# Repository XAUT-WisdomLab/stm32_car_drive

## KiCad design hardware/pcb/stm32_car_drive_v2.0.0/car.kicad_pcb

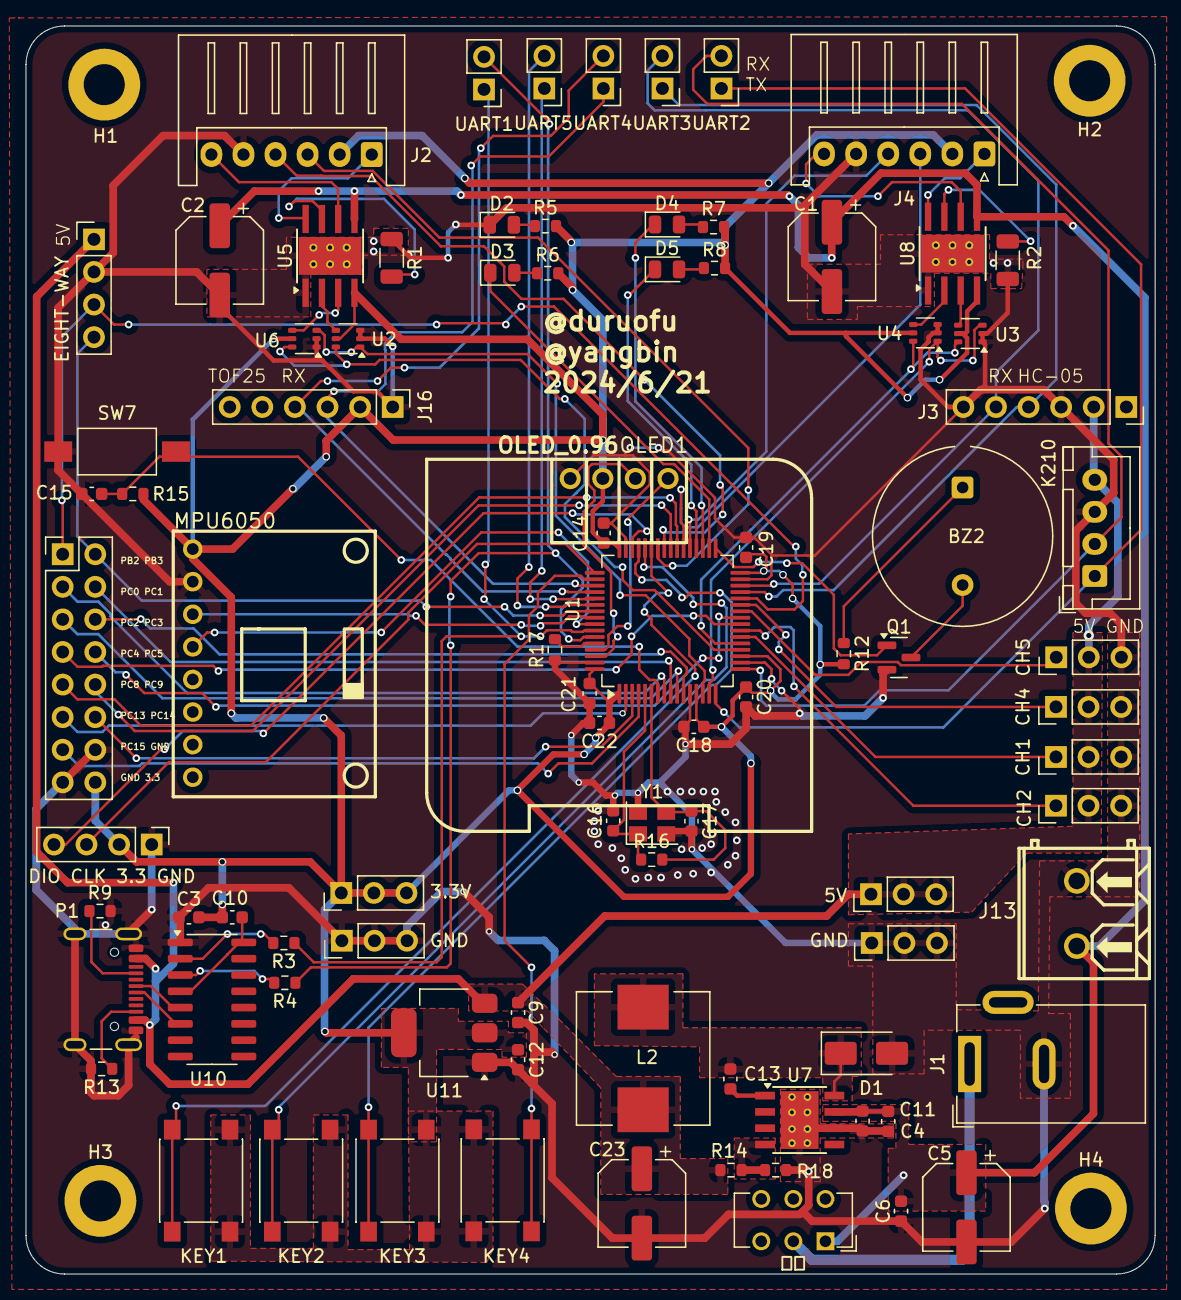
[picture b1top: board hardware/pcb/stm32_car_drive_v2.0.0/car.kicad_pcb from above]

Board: 2 copper layers, 88.0 x 97.3 mm, 92 parts (0 on the bottom side), 84 nets.

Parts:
3.3V, 5V: Conn_01x03; PinHeader_1x03_P2.54mm_Vertical
BZ2: Buzzer; Indicator_PUI_AI-1440-TWT-24V-2-R
C1, C2: 100uf; CP_Elec_6.3x7.7
C3: 0.1uF; C_0603_1608Metric
C4, C11: 4.7uf; C_0603_1608Metric
C5, C23: 220uf; CP_Elec_6.3x7.7
C6, C10: 0.1uf; C_0603_1608Metric
C9, C12: 2.2uF; C_0603_1608Metric
C13: 0.01uf; C_0603_1608Metric
C14, C18, C19, C20, C21, C22: 0.1uf/16V; C_0603_1608Metric
C15: 0.1uF/50V; C_0603_1608Metric
C16, C17: 22pf/16V; C_0603_1608Metric
CH1, CH2, CH4, CH5: Conn_01x03; PinHeader_1x03_P2.54mm_Vertical
D1: B340; D_SMA
D2, D3, D4, D5: LED; LED_0805_2012Metric
DIO CLK 3.3 GND: Conn_01x04; PinHeader_1x04_P2.54mm_Vertical
EIGHT-WAY: Conn_01x04; PinHeader_1x04_P2.54mm_Vertical
GND: Conn_01x03; PinHeader_1x03_P2.54mm_Vertical
GND#2: Conn_01x03; PinHeader_1x03_P2.54mm_Vertical
H1, H2, H3, H4: MountingHole; MountingHole_3.2mm_M3_DIN965_Pad
J1: DC母座(大)
J2, J4: Conn_01x06; JST_XH_S6B-XH-A_1x06_P2.50mm_Horizontal
J3: HC-05; PinSocket_1x06_P2.54mm_Vertical
J13: Conn_01x02; CONN-TH_2P-P5.08
J16: HC-05; PinHeader_1x06_P2.54mm_Vertical
K210: Conn_01x04; JST_XH_B4B-XH-A_1x04_P2.50mm_Vertical
KEY1: K1; SW_Push_1P1T_NO_6x6mm
KEY2: K2; SW_Push_1P1T_NO_6x6mm
KEY3: K3; SW_Push_1P1T_NO_6x6mm
KEY4: K4; SW_Push_1P1T_NO_6x6mm
L2: 22uh; L_Wuerth_HCI-1040
MPU6050: Conn_01x08; MPU6050-GY-521
OLED1: OLED_0.96; 0.96OLED_4P
P1: USB_C_Plug_USB2.0; USB_C_Receptacle_GCT_USB4105-xx-A_16P_TopMnt_Horizontal
PB2 PB3: Conn_02x08_Counter_Clockwise; PinHeader_2x08_P2.54mm_Vertical
Q1: S8050; SOT-23
R1, R2: 0.15R 1206 1WOCP=3.3V/10/0.15R=2.2A; R_1206_3216Metric
R3, R4: 0; R_0603_1608Metric
R5, R6, R7, R8, R17: 10k; R_0603_1608Metric
R9, R13: 5.1K; R_0603_1608Metric
R12: 20; R_0603_1608Metric
R14: R; R_0603_1608Metric
R15: 10K; R_0603_1608Metric
R16: 1M; R_0603_1608Metric
R18: 3.2k; R_0603_1608Metric
SW7: RST; SW_SPST_FSMSM
U1: STM32F103RCTx; LQFP-64_10x10mm_P0.5mm
U2, U3, U4, U6: SOT-363_SC-70-6
U5, U8: DRV8870DDA; Texas_HTSOP-8-1EP_3.9x4.9mm_P1.27mm_EP2.95x4.9mm_Mask2.4x3.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
U7: TPS5430DDA; TI_SO-PowerPAD-8_ThermalVias
U10: CH340C; SOIC-16_3.9x9.9mm_P1.27mm
U11: SGM2212-3.3XKC3G/TR; SOT-223
UART1, UART2, UART3, UART4, UART5: Conn_01x02; PinHeader_1x02_P2.54mm_Vertical
Y1: Crystal_GND24(8M); Crystal_SMD_3225-4Pin_3.2x2.5mm
电源: SW_Push_SPDT; SW_CuK_JS202011CQN_DPDT_Straight

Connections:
+3.3V: 3.3V.1, 3.3V.2, 3.3V.3, C3.2, C10.2, C12.1, C14.1, C18.1, C19.1, C20.1, C21.1, C22.1, DIO CLK 3.3 GND.2, J2.2, J4.2, J16.2, KEY1.2, KEY2.2, KEY3.2, KEY4.2, MPU6050.1, OLED1.2 (VCC), PB2 PB3.16, R5.2, R6.2, R7.2, R8.2, R12.2, R15.2, U1.1 (VBAT), U1.13 (VDDA), U1.19 (VDD), U1.32 (VDD), U1.48 (VDD), U1.64 (VDD), U2.5, U3.5, U4.5, U5.4 (VREF), U6.5, U8.4 (VREF), U11.2 (VOUT), U11.4 (VOUT)
+5V: 5V.1, 5V.2, 5V.3, C9.1, C23.1, CH1.2, CH2.2, CH4.2, CH5.2, EIGHT-WAY.1, J3.2, K210.4, L2.2, P1.A4 (VBUS), P1.A9 (VBUS), P1.B4 (VBUS), P1.B9 (VBUS), R14.1, U11.3 (VIN)
+12V: C1.1, C2.1, C4.2, C5.1, C6.2, C11.2, J13.1, U5.5 (VM), U7.7 (VIN), U8.5 (VM), 电源.1 (A)
/-PB2: EIGHT-WAY.3, PB2 PB3.1, U1.28 (PB2)
/-PB3: EIGHT-WAY.4, PB2 PB3.2, U1.55 (PB3)
/-PC0: PB2 PB3.3, U1.8 (PC0)
/-PC1: PB2 PB3.4, U1.9 (PC1)
/-PC2: PB2 PB3.5, U1.10 (PC2)
/-PC3: PB2 PB3.6, U1.11 (PC3)
/-PC4: PB2 PB3.7, U1.24 (PC4)
/-PC5: PB2 PB3.8, U1.25 (PC5)
/-PC8: PB2 PB3.9, U1.39 (PC8)
/-PC9: PB2 PB3.10, U1.40 (PC9)
/-PC13: PB2 PB3.11, U1.2 (PC13)
/-PC14: PB2 PB3.12, U1.3 (PC14)
/-PC15: PB2 PB3.13, U1.4 (PC15)
/Buzzer: Q1.1 (B), U1.33 (PB12)
/DIRA: U1.20 (PA4), U2.6, U6.6
/DIRB: U1.21 (PA5), U3.6, U4.6
/KEY1: KEY1.1, U1.43 (PA10)
/KEY2: KEY2.1, U1.44 (PA11)
/KEY3: KEY3.1, U1.45 (PA12)
/KEY4: KEY4.1, U1.50 (PA15)
/LED1: D3.1 (K), U1.34 (PB13)
/LED2: D4.1 (K), U1.35 (PB14)
/LED3: D5.1 (K), U1.36 (PB15)
/MPU_SCL: MPU6050.3, U1.56 (PB4)
/MPU_SDA: MPU6050.4, U1.57 (PB5)
/OLED_ACL: OLED1.3 (SCL), U1.62 (PB9)
/OLED_SDA: OLED1.4 (SDA), U1.61 (PB8)
/TIM1_CH1: J2.4, U1.41 (PA8)
/TIM1_CH2: J2.3, U1.42 (PA9)
/TIM2_CH1: U1.14 (PA0), U2.1, U6.3
/TIM2_CH2: U1.15 (PA1), U3.3, U4.1
/TIM3_CH1: CH1.1, U1.22 (PA6)
/TIM3_CH2: CH2.1, U1.23 (PA7)
/TIM3_CH3: CH5.1, U1.26 (PB0)
/TIM3_CH4: CH4.1, U1.27 (PB1)
/TIM8_CH1: J4.4, U1.37 (PC6)
/TIM8_CH2: J4.3, U1.38 (PC7)
/USART1_RX: R4.1, U1.59 (PB7), UART1.2
/USART1_TX: R3.1, U1.58 (PB6), UART1.1
/USART2_RX: K210.2, U1.17 (PA3), UART2.2
/USART2_TX: K210.1, U1.16 (PA2), UART2.1
/USART3_RX: J3.5, U1.30 (PB11), UART3.2
/USART3_TX: J3.4, U1.29 (PB10), UART3.1
/USART4_RX: J16.4, U1.52 (PC11), UART4.2
/USART4_TX: J16.3, U1.51 (PC10), UART4.1
/USART5_RX: U1.54 (PD2), UART5.2
/USART5_TX: U1.53 (PC12), UART5.1
/bb68942b/AOUT1: J2.6, U5.6 (OUT1)
/bb68942b/AOUT2: J2.1, U5.8 (OUT2)
/bb68942b/BOUT1: J4.6, U8.6 (OUT1)
/bb68942b/BOUT2: J4.1, U8.8 (OUT2)
/stm32f103rct6/BOOT0: R17.2, U1.60 (BOOT0)
/stm32f103rct6/OSC_IN: C16.1, R16.1, U1.5 (PD0), Y1.1
/stm32f103rct6/OSC_OUT: C17.1, R16.2, U1.6 (PD1), Y1.3
/stm32f103rct6/RST: C15.2, R15.1, SW7.2, U1.7 (NRST)
/stm32f103rct6/SWCLK: DIO CLK 3.3 GND.3, U1.49 (PA14)
/stm32f103rct6/SWDIO: DIO CLK 3.3 GND.4, U1.46 (PA13)
GND: C1.2, C2.2, C3.1, C4.1, C5.2, C6.1, C9.2, C11.1, C12.2, C14.2, C15.1, C16.2, C17.2, C18.2, C19.2, C20.2, C21.2, C22.2, C23.2, CH1.3, CH2.3, CH4.3, CH5.3, D1.2 (A), D2.1 (K), DIO CLK 3.3 GND.1, EIGHT-WAY.2, GND.1, GND.2, GND.3, GND#2.1, GND#2.2, GND#2.3, J1.2, J2.5, J3.3, J3.6, J4.5, J13.2, J16.1, K210.3, MPU6050.2, OLED1.1 (GND), P1.A1 (GND), P1.A12 (GND), P1.B1 (GND), P1.B12 (GND), P1.S1 (SHIELD), PB2 PB3.14, PB2 PB3.15, Q1.2 (E), R1.1, R2.1, R9.2, R13.2, R17.1, R18.2, SW7.1, U1.12 (VSSA), U1.18 (VSS), U1.31 (VSS), U1.47 (VSS), U1.63 (VSS), U2.2, U2.3, U3.1, U3.2, U4.2, U4.3, U5.1 (GND), U5.9 (GND), U6.1, U6.2, U7.6 (GND), U7.9 (GNDPAD), U8.1 (GND), U8.9 (GND), U10.1 (GND), U11.1 (GND), Y1.2, Y1.4
unnamed: BZ2.2 (+), Q1.3 (C)
unnamed: BZ2.1 (-), R12.1
unnamed: C13.2, D1.1 (K), L2.1, U7.8 (PH)
unnamed: D2.2 (A), R5.1
unnamed: D3.2 (A), R6.1
unnamed: D4.2 (A), R7.1
unnamed: D5.2 (A), R8.1
unnamed: P1.A5 (CC), R9.1
unnamed: P1.A6 (D+), U10.5 (UD+)
unnamed: P1.A7 (D-), U10.6 (UD-)
unnamed: P1.B5 (VCONN), R13.1
unnamed: J1.1, 电源.2 (B)
unnamed: U5.3 (IN1), U6.4
unnamed: U2.4, U5.2 (IN2)
unnamed: R1.2, U5.7 (ISEN)
unnamed: C13.1, U7.1 (BOOT)
unnamed: R14.2, R18.1, U7.4 (VSENSE)
unnamed: U3.4, U8.3 (IN1)
unnamed: U4.4, U8.2 (IN2)
unnamed: R2.2, U8.7 (ISEN)
unnamed: R4.2, U10.3 (RXD)
unnamed: R3.2, U10.2 (TXD)
unnamed: C10.1, U10.4 (V3), U10.16 (VCC)

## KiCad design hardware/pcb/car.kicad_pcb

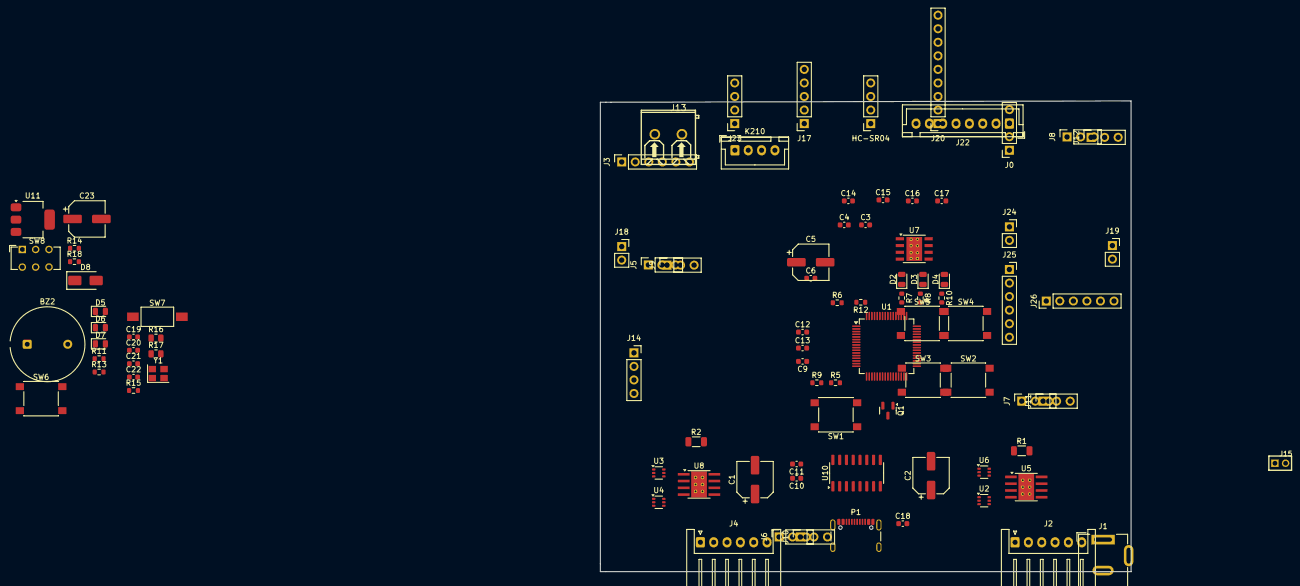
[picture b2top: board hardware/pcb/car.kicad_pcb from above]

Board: 2 copper layers, 99.5 x 88.2 mm, 93 parts (0 on the bottom side), 83 nets, no tracks yet.

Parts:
BZ2: Buzzer; Indicator_PUI_AI-1440-TWT-24V-2-R
C1, C2: 100uf; CP_Elec_6.3x7.7
C3: 0.1uF; C_0603_1608Metric
C4, C11: 4.7uf; C_0603_1608Metric
C5, C23: 220uf; CP_Elec_6.3x7.7
C6, C10: 0.1uf; C_0603_1608Metric
C9, C12: 2.2uF; C_0603_1608Metric
C13: 0.01uf; C_0603_1608Metric
C14, C18, C19, C20, C21, C22: 0.1uf/16V; C_0603_1608Metric
C15: 0.1uF/50V; C_0603_1608Metric
C16, C17: 22pf/16V; C_0603_1608Metric
D2, D3, D4, D5, D6, D7: LED; LED_0805_2012Metric
D8: B340; D_SMA
HC-SR04: HC-SR04; PinSocket_1x04_P2.54mm_Vertical
J0, J14: OLED; PinSocket_1x04_P2.54mm_Vertical
J1: DC母座(大)
J2, J4: Conn_01x06; JST_XH_S6B-XH-A_1x06_P2.50mm_Horizontal
J3, J25: HC-05; PinSocket_1x06_P2.54mm_Vertical
J5, J6, J7, J8, J9, J10, J11, J12: Conn_01x03; PinSocket_1x03_P2.54mm_Vertical
J13: Conn_01x02; CONN-TH_2P-P5.08
J15: Conn_01x02; HDR-TH_2P-P2.00-V-F-1
J17: Conn_01x05; PinSocket_1x05_P2.54mm_Vertical
J18, J19, J24: Conn_01x02; PinSocket_1x02_P2.54mm_Vertical
J20: Conn_01x09; PinSocket_1x09_P2.54mm_Vertical
J22: Conn_01x10; JST_XH_B8B-XH-A_1x08_P2.50mm_Vertical
J23: Conn_01x04; PinSocket_1x04_P2.54mm_Vertical
J26: Conn_01x08; PinHeader_1x06_P2.54mm_Vertical
K210: Conn_01x04; JST_XH_B4B-XH-A_1x04_P2.50mm_Vertical
P1: USB_C_Plug_USB2.0; USB_C_Receptacle_GCT_USB4105-xx-A_16P_TopMnt_Horizontal
Q1: S8050; SOT-23
R1, R2: 0.15R 1206 1WOCP=3.3V/10/0.15R=2.2A; R_1206_3216Metric
R5, R6, R7, R8, R10, R11: 10k; R_0603_1608Metric
R9, R13: 5.1K; R_0603_1608Metric
R12: 20; R_0603_1608Metric
R14: R; R_0603_1608Metric
R15: 10K; R_0603_1608Metric
R16: 1M; R_0805_2012Metric
R17: 10k; R_0805_2012Metric
R18: 3.2k; R_0603_1608Metric
SW1: K1; SW_Push_1P1T_NO_6x6mm
SW2: K2; SW_Push_1P1T_NO_6x6mm
SW3: K3; SW_Push_1P1T_NO_6x6mm
SW4: K6; SW_Push_1P1T_NO_6x6mm
SW5: K5; SW_Push_1P1T_NO_6x6mm
SW6: K4; SW_Push_1P1T_NO_6x6mm
SW7: RST; SW_SPST_FSMSM
SW8: SW_Push_SPDT; SW_CuK_JS202011CQN_DPDT_Straight
U1: STM32F103RCTx; LQFP-64_10x10mm_P0.5mm
U2, U3, U4, U6: SOT-363_SC-70-6
U5, U8: DRV8870DDA; Texas_HTSOP-8-1EP_3.9x4.9mm_P1.27mm_EP2.95x4.9mm_Mask2.4x3.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
U7: TPS5430DDA; TI_SO-PowerPAD-8_ThermalVias
U10: CH340C; SOIC-16_3.9x9.9mm_P1.27mm
U11: SGM2212-3.3XKC3G/TR; SOT-223
Y1: Crystal_GND24(8M); Crystal_SMD_3225-4Pin_3.2x2.5mm

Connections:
+3.3V: C3.2, C10.2, C12.1, C14.1, C18.1, C19.1, C20.1, C21.1, C22.1, J0.2, J2.2, J4.2, J9.1, J9.2, J9.3, J10.1, J10.2, J10.3, J14.2, J23.2, R5.2, R6.2, R7.2, R8.2, R10.2, R11.2, R12.2, R15.2, U1.1 (VBAT), U1.13 (VDDA), U1.19 (VDD), U1.32 (VDD), U1.48 (VDD), U1.64 (VDD), U2.5, U3.5, U4.5, U5.4 (VREF), U6.5, U8.4 (VREF), U11.2 (VOUT), U11.4 (VOUT)
+3V3: SW1.2, SW2.2, SW3.2, SW4.2, SW5.2, SW6.2
+5V: C9.1, C23.1, HC-SR04.4, J3.2, J11.1, J11.2, J11.3, J12.1, J12.2, J12.3, J22.2, J25.2, J26.1, K210.4, P1.A4 (VBUS), P1.A9 (VBUS), P1.B4 (VBUS), P1.B9 (VBUS), R14.1, U11.3 (VIN)
+12V: C1.1, C2.1, C4.2, C5.1, C6.2, C11.2, J13.1, SW8.1 (A), U5.5 (VM), U7.7 (VIN), U8.5 (VM)
/PA0: J4.3, U1.14 (PA0)
/PA1: J4.4, U1.15 (PA1)
/PA2: J24.1, K210.1, U1.16 (PA2)
/PA3: J24.2, K210.2, U1.17 (PA3)
/PA4: J17.1, U1.20 (PA4)
/PA5: J17.2, U1.21 (PA5)
/PA6: J17.3, U1.22 (PA6)
/PA7: J17.4, U1.23 (PA7)
/PA8: D3.1 (K), U1.41 (PA8), U2.1, U6.3
/PA9: U1.42 (PA9), U3.3, U4.1
/PA10: SW1.1, U1.43 (PA10)
/PA11: SW2.1, U1.44 (PA11), U10.2 (TXD)
/PA12: SW3.1, U1.45 (PA12), U10.3 (RXD)
/PA15: J20.7, U1.50 (PA15)
/PB0: J22.5, U1.26 (PB0)
/PB1: J22.4, U1.27 (PB1)
/PB2: J22.3, U1.28 (PB2)
/PB3: D4.1 (K), U1.55 (PB3)
/PB4: J2.3, J20.2, U1.56 (PB4)
/PB5: J2.4, J20.3, U1.57 (PB5)
/PB6: J18.1, U1.58 (PB6)
/PB7: J18.2, U1.59 (PB7)
/PB8: J0.3, J14.3, J25.6, J26.3, U1.61 (PB8)
/PB9: J0.4, J14.4, J25.5, J26.4, U1.62 (PB9)
/PB10: J3.4, J19.1, U1.29 (PB10)
/PB11: J3.5, J19.2, U1.30 (PB11)
/PB12: HC-SR04.2, Q1.1 (B), U1.33 (PB12)
/PB13: SW4.1, U1.34 (PB13)
/PB14: HC-SR04.3, SW5.1, U1.35 (PB14)
/PB15: SW6.1, U1.36 (PB15)
/PC2: J22.8, U1.10 (PC2)
/PC3: J22.7, U1.11 (PC3)
/PC4: J20.6, U1.24 (PC4)
/PC5: J22.6, U1.25 (PC5)
/PC6: J20.8, U1.37 (PC6)
/PC7: J20.9, U1.38 (PC7)
/PC8: J15.1, U1.39 (PC8)
/PC9: J15.2, U1.40 (PC9)
/PC10: J20.4, J25.3, U1.51 (PC10)
/PC11: J20.5, J25.4, U1.52 (PC11)
/PC12: D6.1 (K), U1.53 (PC12)
/PC13: D7.1 (K), U1.2 (PC13)
/PC14: U1.3 (PC14), U2.6, U6.6
/PC15: U1.4 (PC15), U3.6, U4.6
/PD2: D5.1 (K), U1.54 (PD2)
/bb68942b/AOUT1: J2.6, U5.6 (OUT1)
/bb68942b/AOUT2: J2.1, U5.8 (OUT2)
/bb68942b/BOUT1: J4.6, U8.6 (OUT1)
/bb68942b/BOUT2: J4.1, U8.8 (OUT2)
/stm32f103rct6/BOOT0: R17.2, U1.60 (BOOT0)
/stm32f103rct6/OSC_IN: C16.1, R16.1, U1.5 (PD0), Y1.1
/stm32f103rct6/OSC_OUT: C17.1, R16.2, U1.6 (PD1), Y1.3
/stm32f103rct6/RST: C15.2, R15.1, SW7.2, U1.7 (NRST)
/stm32f103rct6/SWCLK: J23.3, U1.49 (PA14)
/stm32f103rct6/SWDIO: J23.4, U1.46 (PA13)
GND: C1.2, C2.2, C3.1, C4.1, C5.2, C6.1, C9.2, C11.1, C12.2, C14.2, C15.1, C16.2, C17.2, C18.2, C19.2, C20.2, C21.2, C22.2, C23.2, D2.1 (K), D8.2 (A), HC-SR04.1, J0.1, J1.2, J2.5, J3.3, J3.6, J4.5, J5.1, J5.2, J5.3, J6.1, J6.2, J6.3, J7.1, J7.2, J7.3, J8.1, J8.2, J8.3, J13.2, J14.1, J17.5, J20.1, J22.1, J23.1, J25.1, J26.2, K210.3, P1.A1 (GND), P1.A12 (GND), P1.B1 (GND), P1.B12 (GND), P1.S1 (SHIELD), Q1.2 (E), R1.1, R2.1, R9.2, R13.2, R17.1, R18.2, SW7.1, U1.12 (VSSA), U1.18 (VSS), U1.31 (VSS), U1.47 (VSS), U1.63 (VSS), U2.2, U2.3, U3.1, U3.2, U4.2, U4.3, U5.1 (GND), U5.9 (GND), U6.1, U6.2, U7.6 (GND), U7.9 (GNDPAD), U8.1 (GND), U8.9 (GND), U10.1 (GND), U11.1 (GND), Y1.2, Y1.4
unnamed: BZ2.2 (+), Q1.3 (C)
unnamed: BZ2.1 (-), R12.1
unnamed: D2.2 (A), R5.1
unnamed: D3.2 (A), R6.1
unnamed: D4.2 (A), R7.1
unnamed: D5.2 (A), R8.1
unnamed: D6.2 (A), R10.1
unnamed: D7.2 (A), R11.1
unnamed: C13.2, D8.1 (K), U7.8 (PH)
unnamed: P1.A5 (CC), R9.1
unnamed: P1.A6 (D+), U10.5 (UD+)
unnamed: P1.A7 (D-), U10.6 (UD-)
unnamed: P1.B5 (VCONN), R13.1
unnamed: J1.1, SW8.2 (B)
unnamed: U5.3 (IN1), U6.4
unnamed: U2.4, U5.2 (IN2)
unnamed: R1.2, U5.7 (ISEN)
unnamed: C13.1, U7.1 (BOOT)
unnamed: R14.2, R18.1, U7.4 (VSENSE)
unnamed: U3.4, U8.3 (IN1)
unnamed: U4.4, U8.2 (IN2)
unnamed: R2.2, U8.7 (ISEN)
unnamed: C10.1, U10.4 (V3), U10.16 (VCC)

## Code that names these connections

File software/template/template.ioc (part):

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Mcu.Name=STM32F103R(C-D-E)Tx
Mcu.Package=LQFP64
Mcu.UserName=STM32F103RCTx
PA0-WKUP.Signal=S_TIM2_CH1_ETR
PA1.Signal=S_TIM2_CH2
PA10.GPIOParameters=GPIO_Label
PA10.GPIO_Label=KEY1
PA10.Signal=GPXTI10
PA11.GPIOParameters=GPIO_Label
PA11.GPIO_Label=KEY2
PA11.Signal=GPXTI11
PA12.GPIOParameters=GPIO_Label
PA12.GPIO_Label=KEY3
PA12.Signal=GPXTI12
PA13.Mode=Serial_Wire
PA13.Signal=SYS_JTMS-SWDIO
PA14.Mode=Serial_Wire
PA14.Signal=SYS_JTCK-SWCLK
PA15.GPIOParameters=GPIO_Label
PA15.GPIO_Label=KEY4
PA15.Signal=GPXTI15
PA2.Mode=Asynchronous
PA2.Signal=USART2_TX
PA3.Mode=Asynchronous
PA3.Signal=USART2_RX
PA4.Signal=GPIO_Output
PA5.Signal=GPIO_Output
PA6.Signal=S_TIM3_CH1
PA7.Signal=S_TIM3_CH2
PA8.Signal=S_TIM1_CH1
PA9.Signal=S_TIM1_CH2
PB0.Signal=S_TIM3_CH3
PB1.Signal=S_TIM3_CH4
PB10.Mode=Asynchronous
PB10.Signal=USART3_TX
PB11.Mode=Asynchronous
PB11.Signal=USART3_RX
PB13.GPIOParameters=GPIO_Label
PB13.GPIO_Label=LED1
PB13.Signal=GPIO_Output
PB14.GPIOParameters=PinState,GPIO_Label
PB14.GPIO_Label=LED2
PB14.PinState=GPIO_PIN_SET
PB14.Signal=GPIO_Output
PB15.GPIOParameters=PinState,GPIO_Label
PB15.GPIO_Label=LED3
PB15.PinState=GPIO_PIN_SET
PB15.Signal=GPIO_Output
PB6.Mode=Asynchronous
PB6.Signal=USART1_TX
PB7.Mode=Asynchronous
PB7.Signal=USART1_RX
PB8.GPIOParameters=GPIO_Label
PB8.GPIO_Label=I2C_SDA
PB8.Signal=GPIO_Output
PB9.GPIOParameters=GPIO_Label
PB9.GPIO_Label=I2C_SCL
PB9.Signal=GPIO_Output
PC10.Mode=Asynchronous
PC10.Signal=UART4_TX
PC11.Mode=Asynchronous
PC11.Signal=UART4_RX
PC12.Mode=Asynchronous
PC12.Signal=UART5_TX
PC13-TAMPER-RTC.Signal=GPIO_Output
PC14-OSC32_IN.Signal=GPIO_Output
PC15-OSC32_OUT.Signal=GPIO_Output
PC6.Signal=S_TIM8_CH1
PC7.Signal=S_TIM8_CH2
PD0-OSC_IN.Mode=HSE-External-Oscillator
PD0-OSC_IN.Signal=RCC_OSC_IN
PD1-OSC_OUT.Mode=HSE-External-Oscillator
PD1-OSC_OUT.Signal=RCC_OSC_OUT
PD2.Mode=Asynchronous
PD2.Signal=UART5_RX
RCC.SYSCLKFreq_VALUE=72000000
RCC.SYSCLKSource=RCC_SYSCLKSOURCE_PLLCLK
board=custom

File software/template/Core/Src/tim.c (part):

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
    __HAL_RCC_GPIOA_CLK_ENABLE();
    /**TIM1 GPIO Configuration
    PA8     ------> TIM1_CH1
    PA9     ------> TIM1_CH2
    */
    GPIO_InitStruct.Pin = GPIO_PIN_8|GPIO_PIN_9;
    GPIO_InitStruct.Mode = GPIO_MODE_INPUT;
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
    __HAL_RCC_GPIOC_CLK_ENABLE();
    /**TIM8 GPIO Configuration
    PC6     ------> TIM8_CH1
    PC7     ------> TIM8_CH2
    */
    GPIO_InitStruct.Pin = GPIO_PIN_6|GPIO_PIN_7;
    GPIO_InitStruct.Mode = GPIO_MODE_INPUT;
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  /* USER CODE END TIM2_MspPostInit 0 */
    __HAL_RCC_GPIOA_CLK_ENABLE();
    /**TIM2 GPIO Configuration
    PA0-WKUP     ------> TIM2_CH1
    PA1     ------> TIM2_CH2
    */
    GPIO_InitStruct.Pin = GPIO_PIN_0|GPIO_PIN_1;
    GPIO_InitStruct.Mode = GPIO_MODE_AF_PP;
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    __HAL_RCC_GPIOA_CLK_ENABLE();
    __HAL_RCC_GPIOB_CLK_ENABLE();
    /**TIM3 GPIO Configuration
    PA6     ------> TIM3_CH1
    PA7     ------> TIM3_CH2
    PB0     ------> TIM3_CH3
    PB1     ------> TIM3_CH4
    */
    GPIO_InitStruct.Pin = GPIO_PIN_6|GPIO_PIN_7;
    GPIO_InitStruct.Mode = GPIO_MODE_AF_PP;
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    __HAL_RCC_TIM1_CLK_DISABLE();

    /**TIM1 GPIO Configuration
    PA8     ------> TIM1_CH1
    PA9     ------> TIM1_CH2
    */
    HAL_GPIO_DeInit(GPIOA, GPIO_PIN_8|GPIO_PIN_9);

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    __HAL_RCC_TIM8_CLK_DISABLE();

    /**TIM8 GPIO Configuration
    PC6     ------> TIM8_CH1
    PC7     ------> TIM8_CH2
    */
    HAL_GPIO_DeInit(GPIOC, GPIO_PIN_6|GPIO_PIN_7);

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
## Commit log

2024-05-23 feat(pcb): update v2.0.0
2024-06-18 feat(pcb): 更新PCB封装
2024-06-18 feat(pcb):更新布局
2024-06-22 feat: 生成生产文件
2024-06-22 追加修改
2024-06-29 oled+pwm+led+uart
2024-06-29 rct6
2024-07-10 final
2024-07-12 蜂鸣器+电机+编码器

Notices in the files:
software/template/Core/Src/tim.c:
Copyright (c) 2024 STMicroelectronics.
All rights reserved.
This software is licensed under terms that can be found in the LICENSE file
